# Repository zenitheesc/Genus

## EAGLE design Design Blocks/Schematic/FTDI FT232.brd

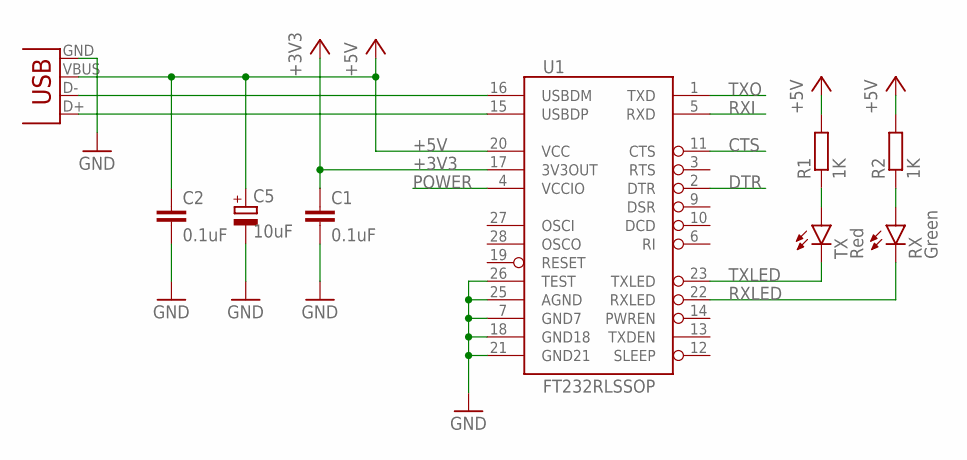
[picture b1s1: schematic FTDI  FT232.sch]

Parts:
C1, C2: 0.1uF; C0805
C5: 10uF; PANASONIC_B
R1, R2: 1K; R0805
RX: Green; CHIPLED_0805
TX: Red; CHIPLED_0805
U1: FT232RLSSOP; SSOP28DB
X2: USB-SMD-NS; USB-MINIB-NOSTOP

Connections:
+3V3: C1.1, U1.17 (3V3OUT)
+5V: C2.1, C5.+, R1.2, R2.2, U1.20 (VCC), X2.VBUS
CTS: U1.11 (CTS)
DTR: U1.2 (DTR)
GND: C1.2, C2.2, C5.-, U1.7 (GND7), U1.18 (GND18), U1.21 (GND21), U1.25 (AGND), U1.26 (TEST), X2.GND
unnamed: R1.1, TX.A
unnamed: R2.1, RX.A
POWER: U1.4 (VCCIO)
RXI: U1.5 (RXD)
RXLED: RX.C, U1.22 (RXLED)
TXLED: TX.C, U1.23 (TXLED)
TXO: U1.1 (TXD)
USB_D+: U1.15 (USBDP), X2.D+
USB_D-: U1.16 (USBDM), X2.D-

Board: 2 copper layers, 9 parts (0 on the bottom side), 9 nets, no tracks yet.

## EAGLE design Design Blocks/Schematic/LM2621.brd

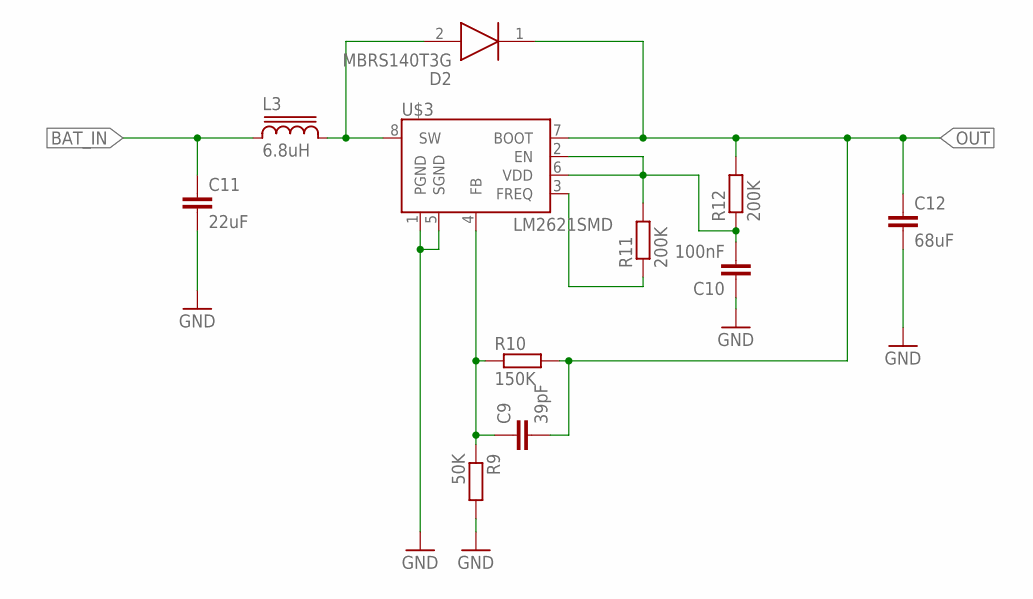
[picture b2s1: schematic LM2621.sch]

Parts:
C9: 39pF; C0805
C10: 100nF; C0805
C11: 22uF; C1210
C12: 68uF; C1210
D2: MBRS140T3G; DIOM5436X247N
L3: 6.8uH; SRR1280
R9: 50K; R0805
R10: 150K; R0805
R11, R12: 200K; R0805
U$3: LM2621SMD; MSOP-8

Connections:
BAT_IN: C11.1, L3.1
GND: C10.1, C11.2, C12.2, R9.2, U$3.1 (PGND), U$3.5 (SGND)
unnamed: C9.1, R9.1, R10.1, U$3.4 (FB)
unnamed: D2.2 (A), L3.2, U$3.8 (SW)
unnamed: C10.2, R11.2, R12.1, U$3.2 (EN), U$3.6 (VDD)
unnamed: R11.1, U$3.3 (FREQ)
OUT: C9.2, C12.1, D2.1 (K), R10.2, R12.2, U$3.7 (BOOT)

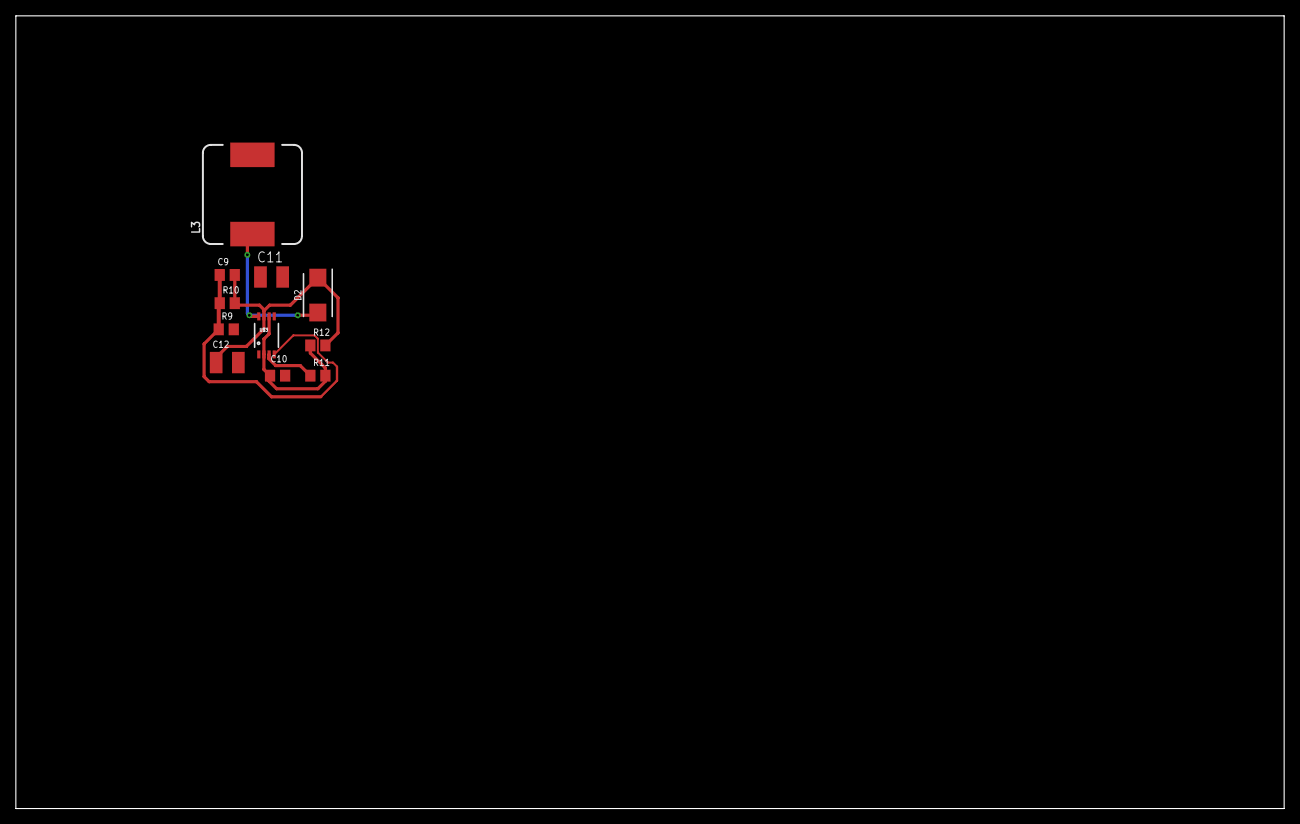
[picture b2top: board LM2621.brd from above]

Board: 2 copper layers, 160.0 x 100.0 mm, 11 parts (0 on the bottom side), 7 nets.

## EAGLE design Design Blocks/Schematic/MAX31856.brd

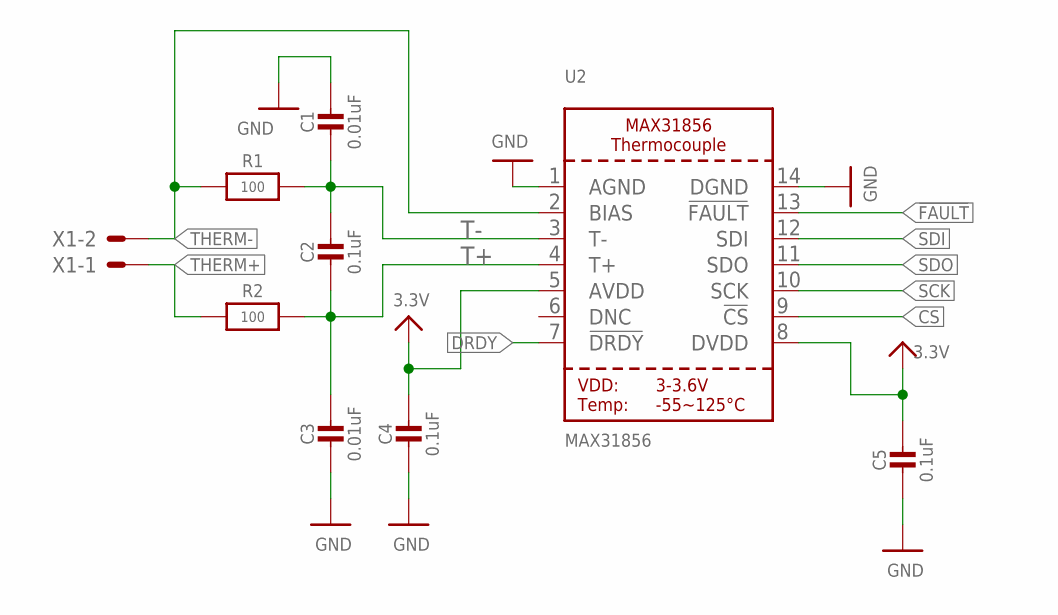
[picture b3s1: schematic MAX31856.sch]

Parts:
C1: 0.01uF; 0805_10MGAP
C2, C4, C5: 0.1uF; 0805-NO
C3: 0.01uF; 0805-NO
R1, R2: 100; 0805-NO
U2: MAX31856; TSSOP14
X1: JST-XH-02-PIN-ROUND-PAD; JST-XH-02-PACKAGE-ROUND-PAD

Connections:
3.3V: C4.1, C5.1, U2.5 (AVDD), U2.8 (DVDD)
!FAULT: U2.13 (!FAULT)
CS: U2.9 (!CS)
DRDY: U2.7 (!DRDY)
GND: C1.1, C3.2, C4.2, C5.2, U2.1 (AGND), U2.14 (DGND)
SCK: U2.10 (SCK)
SDI: U2.12 (SDI)
SDO: U2.11 (SDO)
T+: C2.2, C3.1, R2.2, U2.4 (T+)
T-: C1.2, C2.1, R1.2, U2.3 (T-)
THERM+: R2.1, X1.1
THERM-: R1.1, U2.2 (BIAS), X1.2

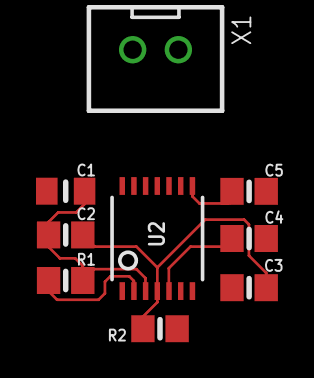
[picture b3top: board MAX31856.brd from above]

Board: 2 copper layers, 9 parts (0 on the bottom side), 6 nets.

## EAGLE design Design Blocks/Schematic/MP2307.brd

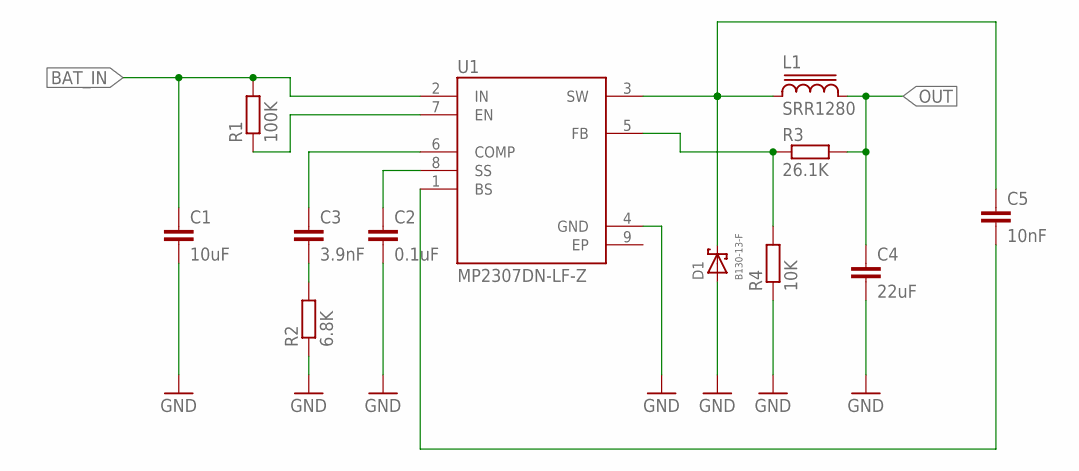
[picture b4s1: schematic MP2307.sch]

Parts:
C1: 10uF; C0805
C2: 0.1uF; C0805
C3: 3.9nF; C0805
C4: 22uF; C0805
C5: 10nF; C0805
D1: B130-13-F; SMA
L1: SRR1280
R1: 100K; R0805
R2: 6.8K; R0805
R3: 26.1K; R0805
R4: 10K; R0805
U1: MP2307DN-LF-Z; SOIC127P600X170-9N

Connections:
BAT_IN: C1.1, R1.2, U1.2 (IN)
EP: U1.9 (EP)
GND: C1.2, C2.2, C4.2, D1.A, R2.1, R4.1, U1.4 (GND)
unnamed: C2.1, U1.8 (SS)
unnamed: R1.1, U1.7 (EN)
unnamed: C3.2, R2.2
unnamed: C3.1, U1.6 (COMP)
unnamed: C5.1, D1.C, L1.1, U1.3 (SW)
unnamed: R3.1, R4.2, U1.5 (FB)
unnamed: C5.2, U1.1 (BS)
OUT: C4.1, L1.2, R3.2

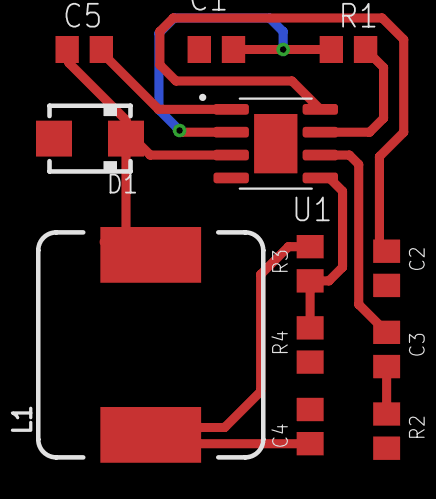
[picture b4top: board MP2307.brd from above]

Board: 2 copper layers, 12 parts (0 on the bottom side), 10 nets.

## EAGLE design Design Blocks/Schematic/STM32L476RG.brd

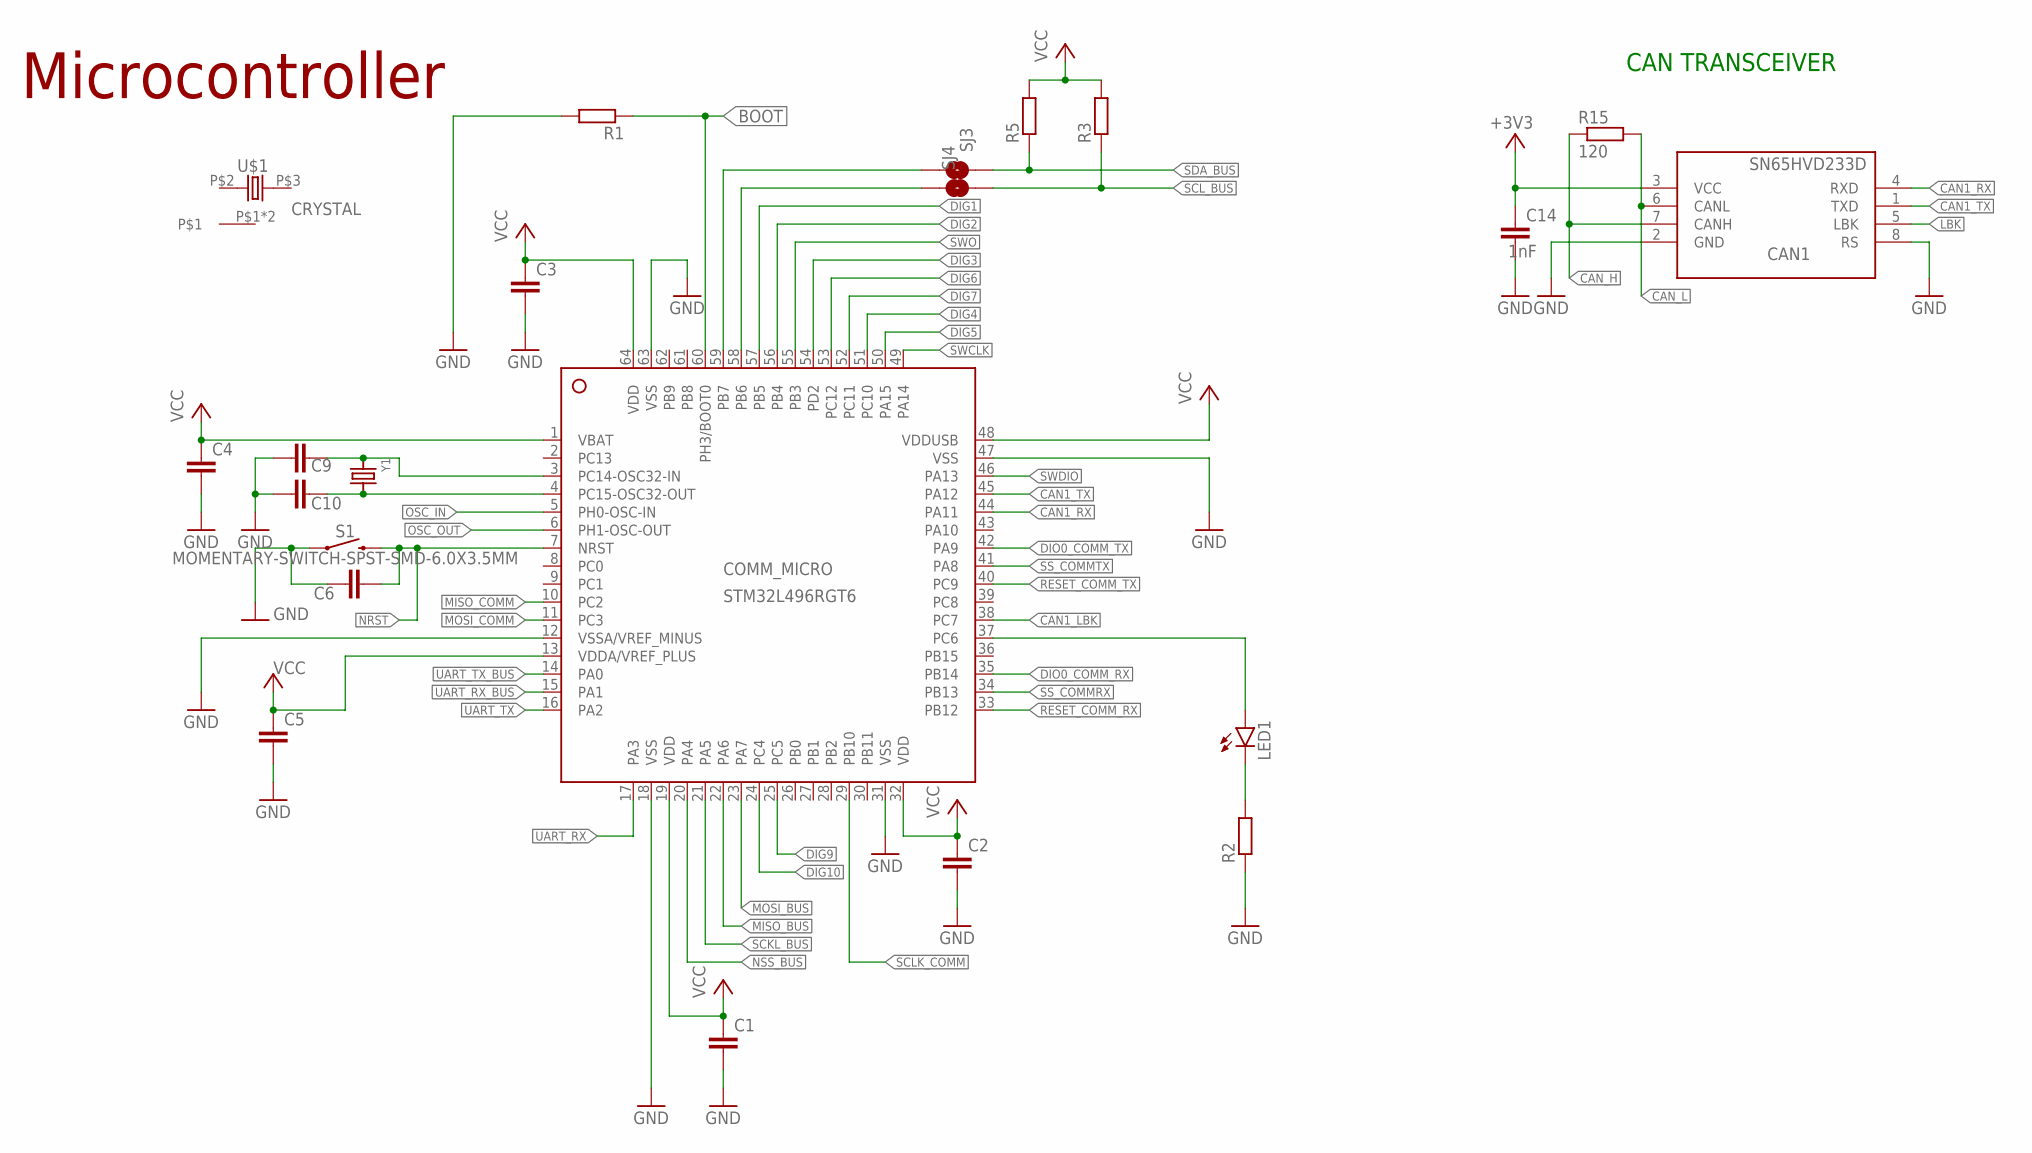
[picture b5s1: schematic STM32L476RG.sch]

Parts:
C1, C2, C3, C4, C5, C6, C9, C10: C-EUC0805; C0805
C14: 1nF; C1206
CAN1: SN65HVD233D; SOIC8
COMM_MICRO: STM32L496RGT6; LQFP64_10X10
LED1: LEDCHIP-LED0805; CHIP-LED0805
R1, R2, R3, R5: R-EU_R0805; R0805
R15: 120; R1206
S1: MOMENTARY-SWITCH-SPST-SMD-6.0X3.5MM; TACTILE_SWITCH_SMD_6.0X3.5MM
SJ3, SJ4: SMD-JUMPER-2
U$1: CRYSTAL; CRYSTAL_SMD
Y1: CRYSTAL8X3.8SMT; CRYSTAL_8X3.8

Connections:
+3V3: C14.1, CAN1.3 (VCC)
BOOT: COMM_MICRO.60 (PH3/BOOT0), R1.1
CAN1_LBK: COMM_MICRO.38 (PC7)
CAN1_RX: CAN1.4 (RXD), COMM_MICRO.44 (PA11)
CAN1_TX: CAN1.1 (TXD), COMM_MICRO.45 (PA12)
CAN_H: CAN1.7 (CANH), R15.1
CAN_L: CAN1.6 (CANL), R15.2
DIG1: COMM_MICRO.57 (PB5)
DIG2: COMM_MICRO.56 (PB4)
DIG3: COMM_MICRO.54 (PD2)
DIG4: COMM_MICRO.51 (PC10)
DIG5: COMM_MICRO.50 (PA15)
DIG6: COMM_MICRO.53 (PC12)
DIG7: COMM_MICRO.52 (PC11)
DIG9: COMM_MICRO.25 (PC5)
DIG10: COMM_MICRO.24 (PC4)
DIO0_COMM_RX: COMM_MICRO.35 (PB14)
DIO0_COMM_TX: COMM_MICRO.42 (PA9)
GND: C1.2, C2.2, C3.2, C4.2, C5.2, C6.1, C9.1, C10.1, C14.2, CAN1.2 (GND), CAN1.8 (RS), COMM_MICRO.12 (VSSA/VREF_MINUS), COMM_MICRO.18 (VSS), COMM_MICRO.31 (VSS), COMM_MICRO.47 (VSS), COMM_MICRO.63 (VSS), R1.2, R2.1, S1.1
LBK: CAN1.5 (LBK)
MISO_BUS: COMM_MICRO.22 (PA6)
MISO_COMM: COMM_MICRO.10 (PC2)
MOSI_BUS: COMM_MICRO.23 (PA7)
MOSI_COMM: COMM_MICRO.11 (PC3)
unnamed: COMM_MICRO.37 (PC6), LED1.A
unnamed: LED1.C, R2.2
unnamed: C9.2, COMM_MICRO.3 (PC14-OSC32-IN), Y1.P$1 (1)
unnamed: C10.2, COMM_MICRO.4 (PC15-OSC32-OUT), Y1.P$4 (2)
unnamed: COMM_MICRO.59 (PB7), SJ3.1
unnamed: COMM_MICRO.58 (PB6), SJ4.1
NRST: C6.2, COMM_MICRO.7 (NRST), S1.2
NSS_BUS: COMM_MICRO.20 (PA4)
OSC_IN: COMM_MICRO.5 (PH0-OSC-IN)
OSC_OUT: COMM_MICRO.6 (PH1-OSC-OUT)
RESET_COMM_RX: COMM_MICRO.33 (PB12)
RESET_COMM_TX: COMM_MICRO.40 (PC9)
SCKL_BUS: COMM_MICRO.21 (PA5)
SCLK_COMM: COMM_MICRO.29 (PB10)
SCL_BUS: R3.1, SJ4.2
SDA_BUS: R5.1, SJ3.2
SS_COMMRX: COMM_MICRO.34 (PB13)
SS_COMMTX: COMM_MICRO.41 (PA8)
SWCLK: COMM_MICRO.49 (PA14)
SWDIO: COMM_MICRO.46 (PA13)
SWO: COMM_MICRO.55 (PB3)
UART_RX: COMM_MICRO.17 (PA3)
UART_RX_BUS: COMM_MICRO.15 (PA1)
UART_TX: COMM_MICRO.16 (PA2)
UART_TX_BUS: COMM_MICRO.14 (PA0)
VCC: C1.1, C2.1, C3.1, C4.1, C5.1, COMM_MICRO.1 (VBAT), COMM_MICRO.13 (VDDA/VREF_PLUS), COMM_MICRO.19 (VDD), COMM_MICRO.32 (VDD), COMM_MICRO.48 (VDDUSB), COMM_MICRO.64 (VDD), R3.2, R5.2

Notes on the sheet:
Microcontroller
CAN TRANSCEIVER

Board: 2 copper layers, 22 parts (0 on the bottom side), 17 nets, no tracks yet.

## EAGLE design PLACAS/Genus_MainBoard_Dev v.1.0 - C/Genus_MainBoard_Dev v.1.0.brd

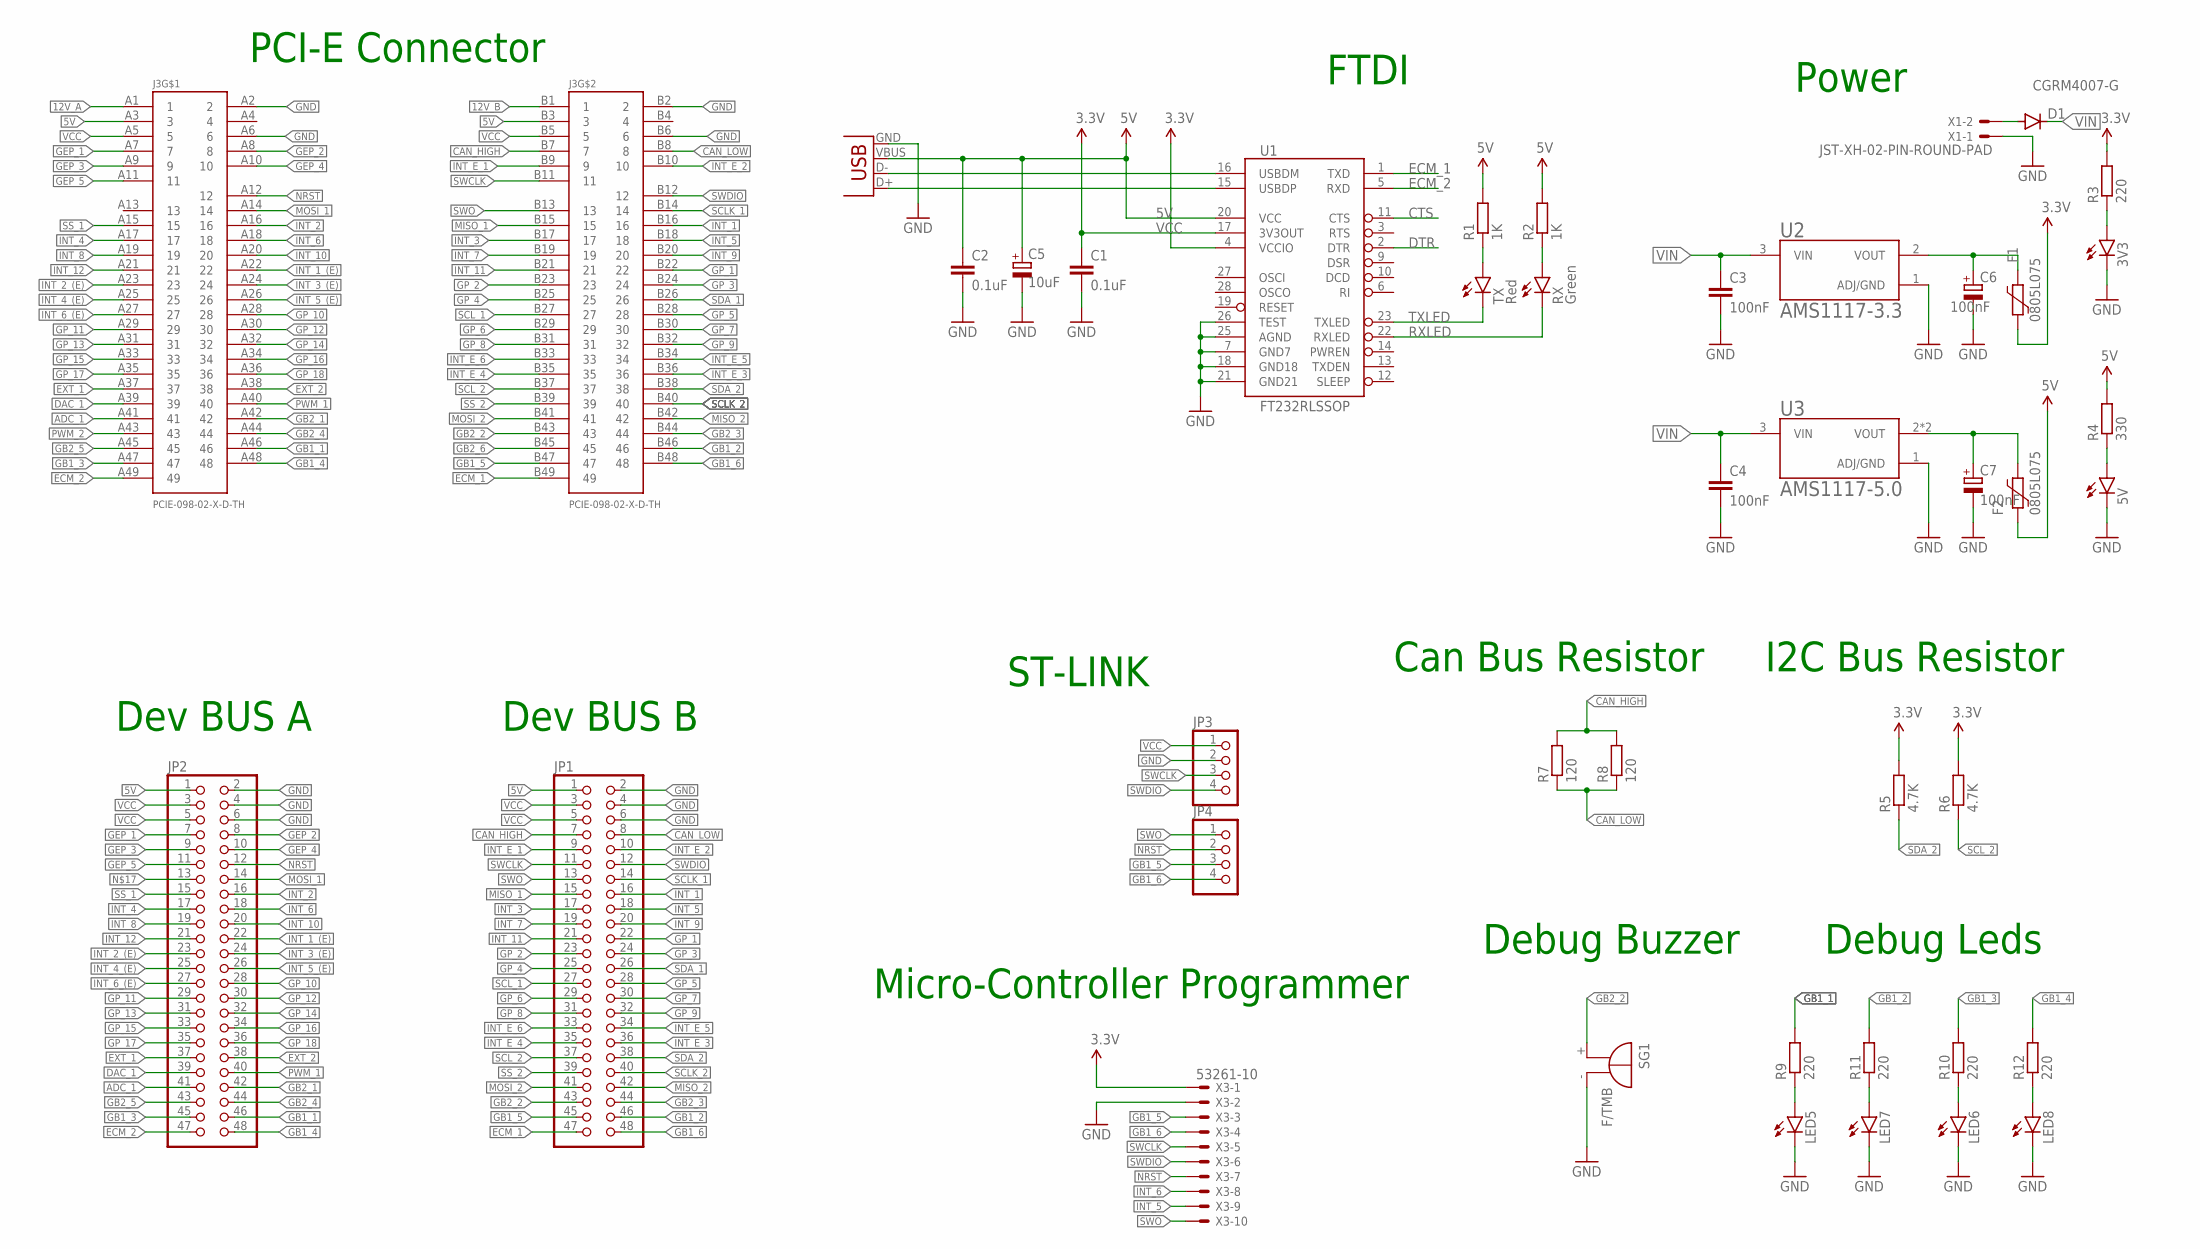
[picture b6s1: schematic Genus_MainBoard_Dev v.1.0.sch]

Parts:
3V3, 5V: LEDCHIPLED_0805; CHIPLED_0805
C1, C2: 0.1uF; C0805
C3, C4: 100nF; C0805
C5: 10uF; PANASONIC_B
C6, C7: 100nF; PANASONIC_B
D1: CGRM4007-G; SOD-123_MINI-SMA
F1, F2: 0805L075; 0805L
J3: PCIE-098-02-X-D-TH
JP1, JP2: PINHD-2X24; 2X24
JP3, JP4: PINHD-1X4; 1X04
LED5, LED6, LED7, LED8: LEDCHIPLED_0805; CHIPLED_0805
R1, R2: 1K; R0805
R3, R9, R10, R11, R12: 220; R0805
R4: 330; R0805
R5, R6: 4.7K; R0805
R7, R8: 120; R0805
RX: Green; CHIPLED_0805
SG1: F/TMB
TX: Red; CHIPLED_0805
U1: FT232RLSSOP; SSOP28DB
U2: AMS1117-3.3; SOT229P700X180-4N
U3: AMS1117-5.0; SOT229P700X180-4N
X1: JST-XH-02-PIN-ROUND-PAD; JST-XH-02-PACKAGE-ROUND-PAD
X2: USB-SMD-NS; USB-MINIB-NOSTOP
X3: 53261-10

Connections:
5V: C2.1, C5.+, F2.2, J3.A3 (3), J3.B3 (3), JP1.1, JP2.1, R1.2, R2.2, R4.2, U1.20 (VCC), X2.VBUS
12V_A: J3.A1 (1)
12V_B: J3.B1 (1)
ADC_1: J3.A41 (41), JP2.41
CAN_HIGH: J3.B7 (7), JP1.7, R7.2, R8.2
CAN_LOW: J3.B8 (8), JP1.8, R7.1, R8.1
CTS: U1.11 (CTS)
DAC_1: J3.A39 (39), JP2.39
DTR: U1.2 (DTR)
ECM_1: J3.B49 (49), JP1.47, U1.1 (TXD)
ECM_2: J3.A49 (49), JP2.47, U1.5 (RXD)
EXT_1: J3.A37 (37), JP2.37
EXT_2: J3.A38 (38), JP2.38
GB1_1: J3.A46 (46), JP2.46, R9.2
GB1_2: J3.B46 (46), JP1.46, R11.2
GB1_3: J3.A47 (47), JP2.45, R10.2
GB1_4: J3.A48 (48), JP2.48, R12.2
GB1_5: J3.B47 (47), JP1.45, JP4.3, X3.3
GB1_6: J3.B48 (48), JP1.48, JP4.4, X3.4
GB2_1: J3.A42 (42), JP2.42
GB2_2: J3.B43 (43), JP1.43, SG1.+
GB2_3: J3.B44 (44), JP1.44
GB2_4: J3.A44 (44), JP2.44
GB2_5: J3.A45 (45), JP2.43
GB2_6: J3.B45 (45)
GEP_1: J3.A7 (7), JP2.7
GEP_2: J3.A8 (8), JP2.8
GEP_3: J3.A9 (9), JP2.9
GEP_4: J3.A10 (10), JP2.10
GEP_5: J3.A11 (11), JP2.11
GND: 3V3.C, 5V.C, C1.2, C2.2, C3.2, C4.2, C5.-, C6.-, C7.-, J3.A2 (2), J3.A6 (6), J3.B2 (2), J3.B6 (6), JP1.2, JP1.4, JP1.6, JP2.2, JP2.4, JP2.6, JP3.2, LED5.C, LED6.C, LED7.C, LED8.C, SG1.-, U1.7 (GND7), U1.18 (GND18), U1.21 (GND21), U1.25 (AGND), U1.26 (TEST), U2.1 (ADJ/GND), U3.1 (ADJ/GND), X1.1, X2.GND, X3.2
GP_1: J3.B22 (22), JP1.22
GP_2: J3.B23 (23), JP1.23
GP_3: J3.B24 (24), JP1.24
GP_4: J3.B25 (25), JP1.25
GP_5: J3.B28 (28), JP1.28
GP_6: J3.B29 (29), JP1.29
GP_7: J3.B30 (30), JP1.30
GP_8: J3.B31 (31), JP1.31
GP_9: J3.B32 (32), JP1.32
GP_10: J3.A28 (28), JP2.28
GP_11: J3.A29 (29), JP2.29
GP_12: J3.A30 (30), JP2.30
GP_13: J3.A31 (31), JP2.31
GP_14: J3.A32 (32), JP2.32
GP_15: J3.A33 (33), JP2.33
GP_16: J3.A34 (34), JP2.34
GP_17: J3.A35 (35), JP2.35
GP_18: J3.A36 (36), JP2.36
INT_1: J3.B16 (16), JP1.16
INT_1_(E): J3.A22 (22), JP2.22
INT_2: J3.A16 (16), JP2.16
INT_2_(E): J3.A23 (23), JP2.23
INT_3: J3.B17 (17), JP1.17
INT_3_(E): J3.A24 (24), JP2.24
INT_4: J3.A17 (17), JP2.17
INT_4_(E): J3.A25 (25), JP2.25
INT_5: J3.B18 (18), JP1.18, X3.9
INT_5_(E): J3.A26 (26), JP2.26
INT_6: J3.A18 (18), JP2.18, X3.8
INT_6_(E): J3.A27 (27), JP2.27
INT_7: J3.B19 (19), JP1.19
INT_8: J3.A19 (19), JP2.19
INT_9: J3.B20 (20), JP1.20
INT_10: J3.A20 (20), JP2.20
INT_11: J3.B21 (21), JP1.21
INT_12: J3.A21 (21), JP2.21
INT_E_1: J3.B9 (9), JP1.9
INT_E_2: J3.B10 (10), JP1.10
INT_E_3: J3.B36 (36), JP1.36
INT_E_4: J3.B35 (35), JP1.35
INT_E_5: J3.B34 (34), JP1.34
INT_E_6: J3.B33 (33), JP1.33
MISO_1: J3.B15 (15), JP1.15
MISO_2: J3.B42 (42), JP1.42
MOSI_1: J3.A14 (14), JP2.14
MOSI_2: J3.B41 (41), JP1.41
unnamed: R1.1, TX.A
unnamed: R2.1, RX.A
unnamed: 3V3.A, R3.1
unnamed: 5V.A, R4.1
unnamed: LED5.A, R9.1
unnamed: LED6.A, R10.1
unnamed: LED7.A, R11.1
unnamed: LED8.A, R12.1
unnamed: D1.A, X1.2
unnamed: C6.+, F1.1, U2.2 (VOUT)
unnamed: C7.+, F2.1, U3.2 (VOUT), U3.4 (VOUT)
NRST: J3.A12 (12), JP2.12, JP4.2, X3.7
PWM_1: J3.A40 (40), JP2.40
PWM_2: J3.A43 (43)
RXLED: RX.C, U1.22 (RXLED)
SCLK_1: J3.B14 (14), JP1.14
SCLK_2: J3.B40 (40), JP1.40
SCL_1: J3.B27 (27), JP1.27
SCL_2: J3.B37 (37), JP1.37, R6.1
SDA_1: J3.B26 (26), JP1.26
SDA_2: J3.B38 (38), JP1.38, R5.1
SS_1: J3.A15 (15), JP2.15
SS_2: J3.B39 (39), JP1.39
SWCLK: J3.B11 (11), JP1.11, JP3.3, X3.5
SWDIO: J3.B12 (12), JP1.12, JP3.4, X3.6
SWO: J3.B13 (13), JP1.13, JP4.1, X3.10
TXLED: TX.C, U1.23 (TXLED)
USB_D+: U1.15 (USBDP), X2.D+
USB_D-: U1.16 (USBDM), X2.D-
VCC: C1.1, F1.2, J3.A5 (5), J3.B5 (5), JP1.3, JP1.5, JP2.3, JP2.5, JP3.1, R3.2, R5.2, R6.2, U1.4 (VCCIO), U1.17 (3V3OUT), X3.1
VIN: C3.1, C4.1, D1.C, U2.3 (VIN), U3.3 (VIN)

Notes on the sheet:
PCI-E Connector
FTDI
Power
Micro-Controller Programmer
ST-LINK
I2C Bus Resistor
Can Bus Resistor
Debug Leds
Debug Buzzer
Dev BUS A
Dev BUS B

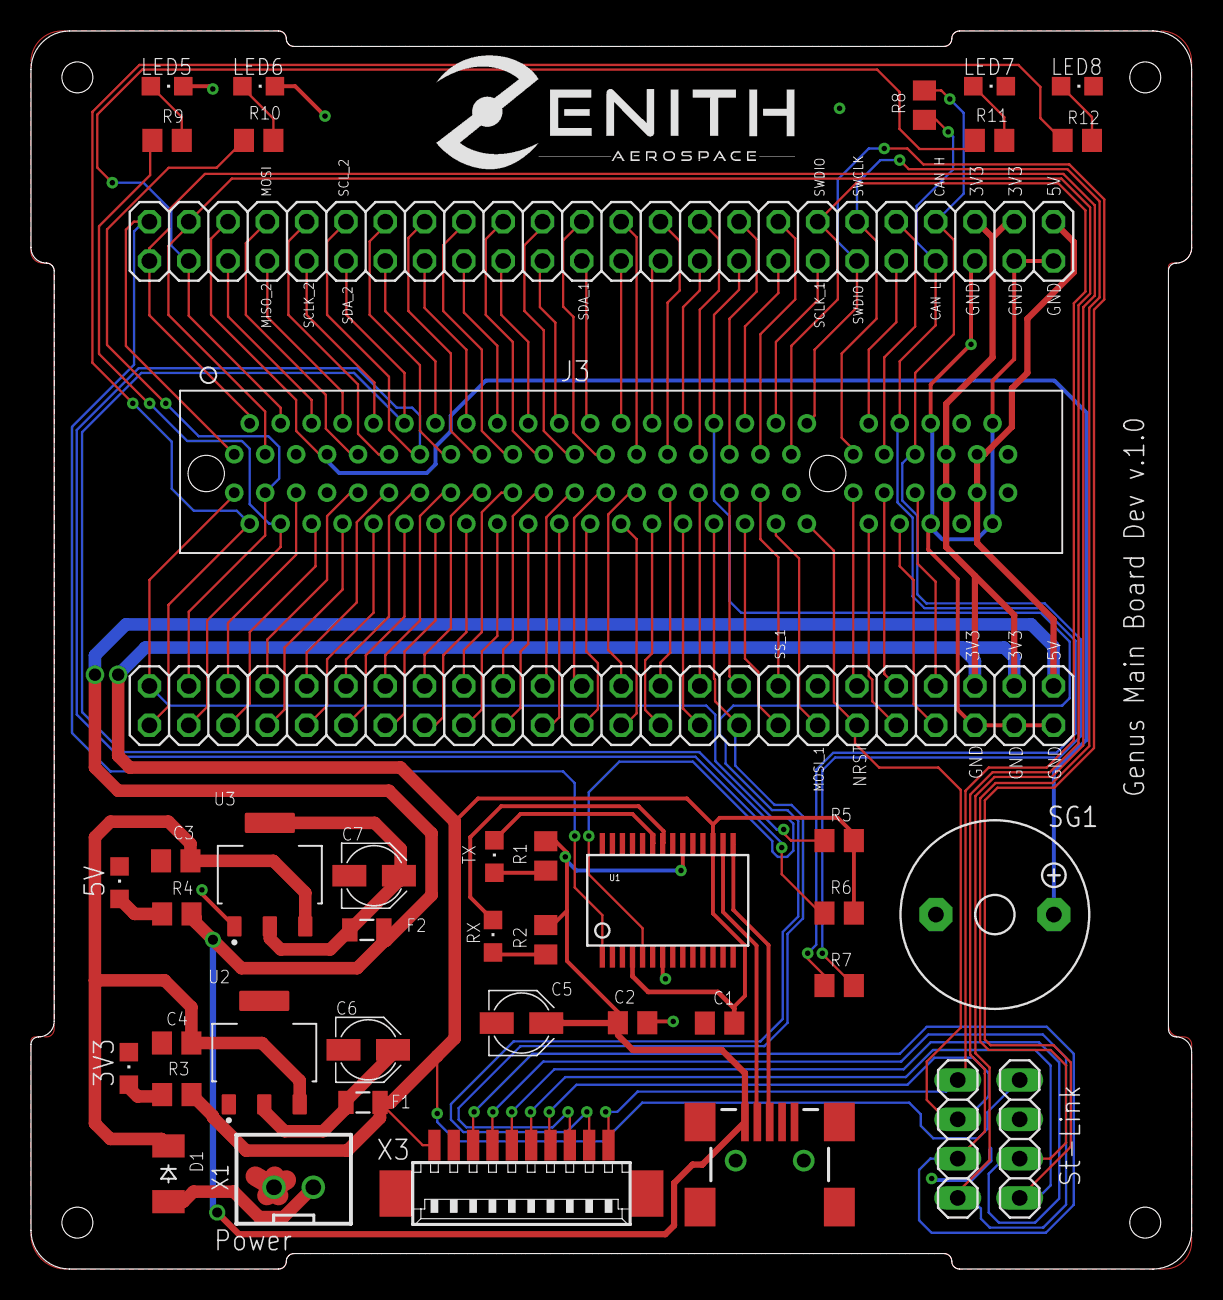
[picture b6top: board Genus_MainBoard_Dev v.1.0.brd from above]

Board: 2 copper layers, 75.0 x 80.0 mm, 42 parts (0 on the bottom side), 102 nets.

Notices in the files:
parts and their libraries:
inductor-bourns: Copyright (C) 2008, Bob Starr
SparkFun-PowerIC: Licensing: Creative Commons ShareAlike 4.0 International - https://creativecommons.org/licenses/by-sa/4.0
FaBo-PIN: Released under the Creative Commons Attribution-ShareAlike 4.0 License
https://creativecommons.org/licenses/by-sa/4.0
